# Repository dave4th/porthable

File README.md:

ATTENZIONE
==========
Il progetto e` in corso, le informazioni contenute in questo repository sono inesatte ed incomplete.

# porthable
Portabile (?) "logger" di temperatura e umidita` con LCD e mdulo ESP8266

Un piccolo esperimento per realizzare un sensore di temperatura che sia movibile per rilevazioni temporanee, che memorizzi le variazioni in un grafico e trasmetta o permetta di leggere da remoto i valori.

Poi .. vedremo in cosa e se .. si evolvera`.

## Composizione/i
* ATMEGA328P (Arduino)
* Sonda temperatura:
    * Sonda di temperatura e umidita` DHT11
    * Sonda di temperatura DS18B20
* TFT LCD 1,44"
* Modulo wifi ESP8266
* Modulo orologio DS1302

# Kicad

Il circuito e` aggiornato (se non ho dimenticato di fare upload ;) ), normalmente anche il ".pdf", per il resto, estrazione materiali, pcb .. eccetera, sono solo delle prove.

# w/ DS1302

Nei 'moduli' con orologio, per prima cosa si deve configurare l'ora, dopo aver collegato all'ATMEGA il DS1302 come da circuito elettrico, caricare sul microcontrollore il programma: "porthable_DS1302_SetSerial".

### Problema DS1302

Se si sostituisce l'atmega (per esempio quando se ne mette uno programmato differente) togliendo completamente alimentazione, lsciando comunque la batteria tampone, il DS1302 sembra vada in blocco e si deve riprogrammare.

Sembra sia sufficiente mantenere alimentazione (o meglio, mantenere il riferimento a 0V) aprendo solo l'interruttore di accensione, quando si sostituisce l'atmega.

## Programmazione con Raspberry Pi

Anzitutto ho creato il ".hex" semplicemente facendo un verifica dall'Arduino IDE 1.6.7, il file viene generato in una sottodirectory "/tmp".

Prima di caricare il programma, scollegate/togliete il Display (perche\` ha dei collegamenti in comune sulla SPI) e il modulo ESP8266 (perche\` e\` collegato sulla seriale), se li avete collegati.

Caricare lo sketch col comando (non serve avere un'ATMEGA col bootloader precaricato):
<pre>sudo avrdude -p m328p -P /dev/spidev0.0 -c linuxspi -b 10000 -U flash:w:git/porthable/arduino/porthable_DS1302_SetSerial.ino.hex</pre>

Con le "python-serial" (http://pyserial.readthedocs.org/en/latest/tools.html#module-serial.tools.miniterm) ho configurato l'ora:
<pre>miniterm.py --cr /dev/ttyAMA0 115200</pre>

Le istruzioni su come procedere all'impostazione dell'ora sono indicate nel ".ino" (che contiene il codice sorgente), comunque basta inserire la stringa "aaaa,mm,gg,HH,MM,SS" (Anno,Mese,Giorno,Hora,Minuti,Secondi).

Questa operazione dovra\` essere ripetuta quando si scarichera` la batteria tampone.

Ora potete procedere caricando sull'ATMEGA il programma vero e proprio ...

# porthable ADLD

Prima versione, composta da:
* ATMEGA328P
* DHT11
* LCD TFT 1,44"
* DS1302

Programmazione ATMEGA328P:
<pre><code>sudo avrdude -p m328p -P /dev/spidev0.0 -c linuxspi -b 10000 -U lfuse:w:0xFF:m -U hfuse:w:0xDE:m -U efuse:w:0x06:m</code></pre>
<pre><code>sudo avrdude -p m328p -P /dev/spidev0.0 -c linuxspi -b 10000 -U flash:w:porthable_adld.ino.hex</code></pre>

Il programma contiene ancora tutti i riferimenti alla configurazione completa, ma sono stati commentati i blocchi inutilizzati.

Lo schema elettrico comprende ancora tutta la circuiteria, e\` sufficiente non collegare quello che non c'e\` o che non si utilizza (vedi programma/sketch).

# porthable ADLE

Seconda versione, composta da:
* ATMEGA328P
* DHT11
* LCD TFT 1,44"
* ESP8266

Il programma e\` stato ampiamente rivisto, ma contiene ancora qualche riferimento alla configurazione completa, sono stati commentati i blocchi inutilizzati.

Lo schema elettrico comprende ancora tutta la circuiteria, e\` sufficiente non collegare quello che non c'e\` o che non si utilizza (vedi programma/sketch).

# porthable AWLD

Versione con sonda 'OneWire', composta da:
* ATMEGA328P
* DS18B20
* LCD TFT 1,44"
* DS1302

Solito, il programma e\` stato modificato mantenendo alcuni riferimenti alla configurazione da cui e\` stato originato (ADLE), sono stati commentati i blocchi inutilizzati.

Il collegamento della sonda 'OneWire' DS18B20 e\` identico al DHT11 (non ho ancora fatto o modificato uno schema elettrico)

Lo schema elettrico comprende ancora tutta la circuiteria, e\` sufficiente non collegare quello che non c'e\` o che non si utilizza (vedi programma/sketch).

# porthable AWLE

Versione con sonda 'OneWire', composta da:
* ATMEGA328P
* DS18B20
* LCD TFT 1,44"
* ESP8266

Solito, il programma e\` stato modificato mantenendo alcuni riferimenti alla configurazione da cui e\` stato originato (AWLE, AWLD), sono stati commentati i blocchi inutilizzati.

Il collegamento della sonda 'OneWire' DS18B20 e\` identico al DHT11 (non ho ancora fatto o modificato uno schema elettrico)

Lo schema elettrico comprende ancora tutta la circuiteria, e\` sufficiente non collegare quello che non c'e\` o che non si utilizza (vedi programma/sketch).

# Update

## Aggiornamenti 2016 01 24

Ho eliminato la seriale software, troppi problemi, collegando l'ESP sulla seriale standard dell'ATMEGA.

Ho aggiunto un potenziometro per selezionare/modificare i tempi di refresh del grafico.

Ho modificato la visualizzazione sul display,
 aggiungendo i tempi grafico e qualche tacca di riferimento,
 forse ho esagerato ..

Il programma testato e\` solamente quello della versione ADLE,
 nell'altro mi sono limitato a copiare le parti, quindi e\` da provare.

Modificato circuito elettrico.

Elimino i ".hex" dal repository github (sapete come ricavarli dai sorgenti ;) )

## Aggiornamenti 2016 01 31

Rimesso ".hex" per comodita\`.

## Aggiornamenti 2016 02 03

Cambiato libreria sensore DHT11 (http://playground.arduino.cc/Main/DHT11Lib).

Modificato aggiornamento data-ora.

Aggiunte memorie di lettura per eliminare le troppe oscillazioni sui valori.

Per ora solo versione ADLE.

# Riferimenti

* http://www.rinkydinkelectronics.com/library.php?id=5
* https://github.com/PaulStoffregen/OneWire

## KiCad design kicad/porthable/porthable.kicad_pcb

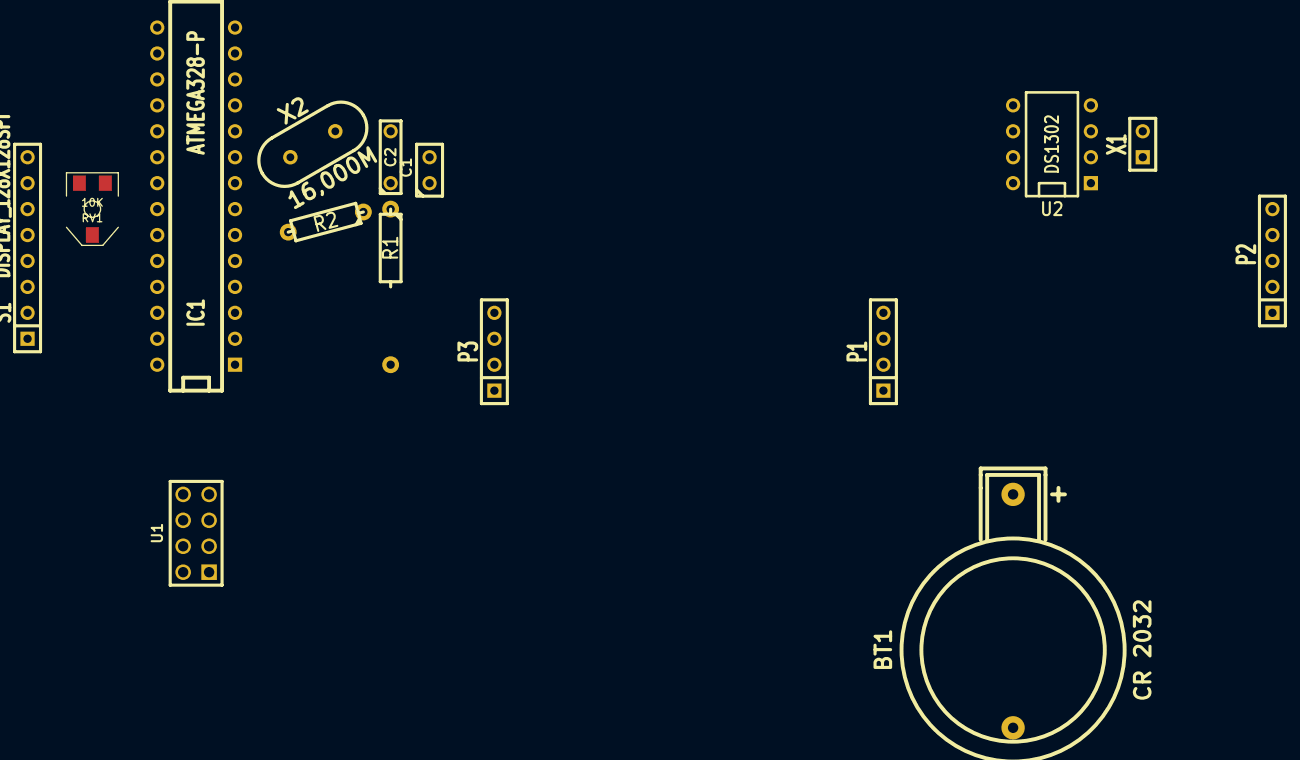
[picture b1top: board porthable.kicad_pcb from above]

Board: 2 copper layers, 15 parts (0 on the bottom side), 20 nets, no tracks yet.

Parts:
BT1: CR 2032; CR2032H
C1: 22pF; C1
C2: 22pF; C2
IC1: ATMEGA328-P; DIP-28__300
P1: DHT11; SIL-4
P2: Program w/R.Pi; SIL-5
P3: Serial; SIL-4
R1: 10K; R3-LARGE_PADS
R2: 4.7K; R3-LARGE_PADS
RV1: 10K; POT_CMS
S1: DISPLAY_128X128SPI; SIL-8
U1: ESP8266; pin_array_4x2
U2: DS1302; DIP-8__300
X1: 323768K; SIL-2
X2: 16,000M; HC-49V

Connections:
GND: BT1.2, C1.1, C2.1, IC1.8, IC1.22, P1.4, P2.5, P3.2, RV1.1, S1.7, U1.2, U2.4
unnamed: IC1.18, P2.3
unnamed: IC1.2, P3.3
unnamed: IC1.3, P3.4
unnamed: U2.3, X1.2
unnamed: IC1.11, U2.5
unnamed: BT1.1, U2.8
unnamed: IC1.6, P1.2, R2.2
unnamed: U2.2, X1.1
unnamed: IC1.23, RV1.2
unnamed: IC1.13, U2.7
unnamed: IC1.4, U1.1
unnamed: IC1.12, U2.6
unnamed: IC1.5, U1.8
unnamed: IC1.7, IC1.20, P1.1, P3.1, R1.1, R2.1, RV1.3, S1.1, S1.8, U1.3, U1.7, U2.1
unnamed: P2.4, S1.2
unnamed: P2.2, S1.3
unnamed: C1.2, IC1.9, X2.1
unnamed: IC1.1, P2.1, R1.2
unnamed: C2.2, IC1.10, X2.2

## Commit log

2015-12-10 ATMEGA328P
2015-12-10 ESP8266
2015-12-10 Kicad
2015-12-12 In funzione da 1 ora
2015-12-12 Update circuit diagram
2015-12-26 ADLD version
2015-12-26 recheck at 30min
2015-12-26 Corretto errori README
2015-12-27 ADLD update
2015-12-27 README update
2016-01-07 New ADLE
2016-01-10 add ADLE Sming program, change gitignore
2016-01-24 + Potenziometro, Indicazioni grafiche
2016-01-24 - hex, aggiunto parametro sming
2016-01-24 Corretto accenti readme
2016-01-31 Serial .hex
2016-01-31 Upload e config serial data
2016-01-31 Corretto .hex
2016-02-03 Memorie lettura, sincronizzazione data-ora, circuito elettrico
2016-02-27 Versione OneWire (DS18B20)
2016-02-28 + AWLE version
2016-02-28 Visualizzazioni grafiche AWLE
2016-03-05 Gerarchia messaggio in mqtt
2016-04-20 Data a MQTT di Livello 1
